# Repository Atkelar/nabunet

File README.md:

# nabunet - Modem and Network Specifications
My idea of a network backend for the "Nabu PC" - based on reverse engineering the old device and boot code...

The big question first: **why?** or **why not join any of the other similar projects?** simple: fun! For
me, most of the fun is the reverse engineering and coming-up-with-solutions phase. So joining some
other project here wouldn't do it for me... it is as simple as that. I hope that my view/take provides
something at least remotely unique and if public interest is low... I'll keep it to myself, but I'll
not stop just because "somebody else already did something similar" :)

## Revisions

  - Initial version, 2023-04-23
  - First steps Firmware/Config program, 2023-05-27
  - First public visible NabuNet server code, 2023-08-25

## References used

  - https://en.wikipedia.org/wiki/NABU_Network
  - https://bitsavers.org/pdf/nabu/Nabu_Computer_Technical_Manual_by_MJP.pdf

Other than those, the only information used was the original chips datasheets; Z-80, TR1863/1865, TMS9918A, AY-3-8910, 9637, 9639 and LS74-logic.

## Introduction

The basic idea for the "modem" is to hook up the Nabu Personal Computer (NPC, Nabu) to the internet.
Since Nabu is an 8-bit system with "just" 64k of RAM and the hookup has to be done via the built in
111kbit serial port, we cannot expect that the NPC is doing any heavy lifting (or any lifting) that
is required to connect to any IP based service directly these days, while still having enough
resources for any functional useful program left. The encryption code and state data alone is probably
eating up all of that RAM.

The modem should - IMHO - also be kept as simple as possible, ideally just forwarding any request
and response to an upstream server. But, at the least, do that already in an encrypted format, so
it supports direct internet connections via established, modern and available connectivity.

So, my idea in a nutshell: do all the required processing in a web service, where resources are plenty,
and let the modem do a very basic, simple translation of the requests/responses.

## High Level Operation

### Booting

The NPC "boots" into a 4k ROM module, although there seem to be 8k versions prepared too. Not sure if
these are ever implemented...

The ROM will initialize the support chips, do a functional check on all components (RAM, ROM, Sound, 
Keyboard and Modem chips) and then start to talk with the modem.

The first request to the modem are (assumed to be) initialization and synchronization commands.

The next command sent will reply with a flag bit either set or cleared to indicate if the modem has
the "channel code" set. This will tune the original cable modem to the appropriate channel but is
only kept in RAM. So a cold boot of the modem will not have that info.

If the modem is lacking the channel code, the NPC prompts the user to enter one. This is a five
digit hex code (00000 to FFFFF) but the last digit is a checksum, resulting in 65536 possible
channels to pick from. No range validation is performed here, and "all zero" is a valid code
that passes the checksum.

Once the channel code is entered, it is sent to the modem and the NPC waits for confirmation.

If either checksum or modem ack fails, the user is prompted to re-enter the code.

Once the modem has the channel code set, the NPC will request the "main program" as a sequence
of blocks. The buffer size that is set aside for loading them led to the assumption that
these blocks are up to 512 bytes in length each, with 16 bytes header and 2 bytes checksum
at the end.

The checksum is a derivative of the CRC-16 CCITT checksum, sometimes referred to as the "BAD"
implementation.

The only header bit used by boot loader is the "completed" bit, that indicates that the transferred
block was the last one of the sequence. Until that one is set, all blocks (without the header!)
are moved into RAM to offset 140Dh and on.

Note that the blocks can have arbitrary sizes, the "end of block" is signalled with a terminating
"10h" byte, followed by any other byte than "10h", with "0E1h" indicating success. Thus, the byte
sequence "10h E1h" terminates the block. To include a "10h" byte inside the payload, it has to
be escaped, i.e. "10h 10h" results in one "10h" byte to be loaded and checksum'd.

Once all blocks are received, the ROM is copied into the same RAM address and turned off, making
the byte range R/W from regular RAM but keeping the ROM code intact for rebooting the system. 
Execution is then passed to address 140Fh - note that it is two bytes AFTER the load offset and 
a rather odd address to start from...

### Boot loader code and "OS" idea...

To use the built in boot loader, we have to make use of the channel code somehow; my idea is to 
have the "00000" code provide a basic "initialize modem parameters" program. This is easy to
remember and can be used to set up the internet facing parameters, like server address to use,
SSID and key for WiFi, IP config for wired... these type of things.

Once set up, the modem can "pretend" to know the channel code, thus skipping the prompt.

To re-configure the modem, it should have a type of "reset" button; while a simple modem
reboot would serve the same purpose, I think it's a better idea to allow storing the modem
config in NVRAM somewhere to avoid the rather lengthy server/IP config every time...

The program provided for a known channel ID can then already be a "core OS", provided either
in parts or completely by the selected server.

### Security?!

Note: Any mandatory login or authentication beyond the server configuration is.. well...
taking away from the immersion of "ye-old-device". To keep the server somewhat secure and
proper suited for a modern internet with lots of bad players, the access to the information
available via the modem is considered "mostly read only" and "public"!

Once the modem is connected to the server with the proper credentials validated, the modem
will run with a simple "shared access token" against that server. This is by no means
"secure" and thus no highly sensitive information should ever be stored inside that 
environment! I'm talking personal information like credit card numbers and similar things.

Passing such information through the network to a server sided "callback" that does not
store anything inside the NPC accessible ranges should be fine, since the modem would
connect to the server via TLS... This still needs a proper security analysis of the
finished system though, so better assume that anything you enter into an application
will eventually become "public".

### Servers...

It is possible to use "physical" and "logical" servers. In order to function, the 
"channel zero" initialization has to point the modem to a physical server. During the
setup and configuration phase, that server can tell the modem if it supports "virtual"
servers. To keep the specs simple, there can be up to "FFF0h" virtual servers defined
per physical server, the numbers 1-F being reserved for "internal servers" if this
feature is enabled on the physical server... I'm thinking of "developer" and "diag"
servers mostly... If the physical server does NOT support virtual servers, it is
automaticalls assumed to be a single pre-selected virtual server for the rest of this
specification.

### Virtual Server

Each virtual server is a walled off environment, akin to a cable network. The main
purpose is to provide individual OS kernels during the boot process.

To switch to a differnet virtual server, a special reboot command is needed to tell
the modem to "forget" the current channel code. When the user is then prompted to
re-type the channel code, they can either use 00000 to go to the physical configuration
or any other number - if supported - to switch to another virtual server. The ROM
code doesn't have that provision to "force selection", this has to be done with
a flag in the modem;

I am also considering to have a "Nabu compatible" mode that keeps the communication 
between NPC and Modem 100% compatible with the original protocol, but that depends 
on me FINDING the specs for that protocol first... the problem here is that I don't
know if the original software would have an option to re-enter the channel code?
At worst case, the modem reset button would have to be used...

### DOS or not DOS?

The specs call the OS "DOS" for "Downloadable OS"... in contrast to the integrated
OS that boots the system. I am working on a reasonable implementation for simple
access to the different screen modes, sound chip and peripherals like the printer
port. My goal is to keep that OS below at least the 32k boundary, so the upper 32k
would always be available for program code. This doesn't sound like much, but keep
in mind that "loading a block from tape" or similar can now be considered "load
a block from the internet" at speeds that these devices are not used to. I think
almost any program can be made like that; The final decision on the memory 
requirements of the OS kernel are not set yet, so it might as well be much more.

Programs that make use of that "standard OS" could have simplified load code
provided, with a program browser as an initial app loaded from the server...

### R/W access?

A downside of the original NPC was the lack of storage space. But this is the age
of "cloud computing"... as much as I personally dislike that concept, it does
fit well with this system. During connection of the NPC with the server, personal
user info can be provided (think user/password) and when successful, the server
can provide storage space for that account. Note that the physical server can
choose if that space applies to logical servers and what part is server specific...
NPC doesn't see that difference. This would allow programs like - e.g. - a BASIC
interpreter to save/load programs from a "virtual disk" with ease.

To keep the stored information as secure as possible, the server will allow access
based on an access policy (private, server only, public) based on "virtual disk"
units. This would allow sharing information or keeping it private.

The resulting security model would however make it possible to use a guessed or
hijacked token to write to or just erase that information... to safeguard against
that possibility, a "snapshot" based system should be implemented on the server,
where these snapshots are invisible to the NPC and only controllable via the regular
internet facing, browser based management UI of your account. This should mitigate
any "attack" to the "less secure" data inside your Nabu Storage...

### Server software

Once sufficiently mature - i.e. as soon as it works at least a little bit :) - the 
server software along with the core OS will be published here as an open source 
project.

The overall concept would see it that anybody can code against the NPC and provide
their applications to the server(s) running this software.

I am - naturally - looking into hosting one of these myself as a "central default"
server...

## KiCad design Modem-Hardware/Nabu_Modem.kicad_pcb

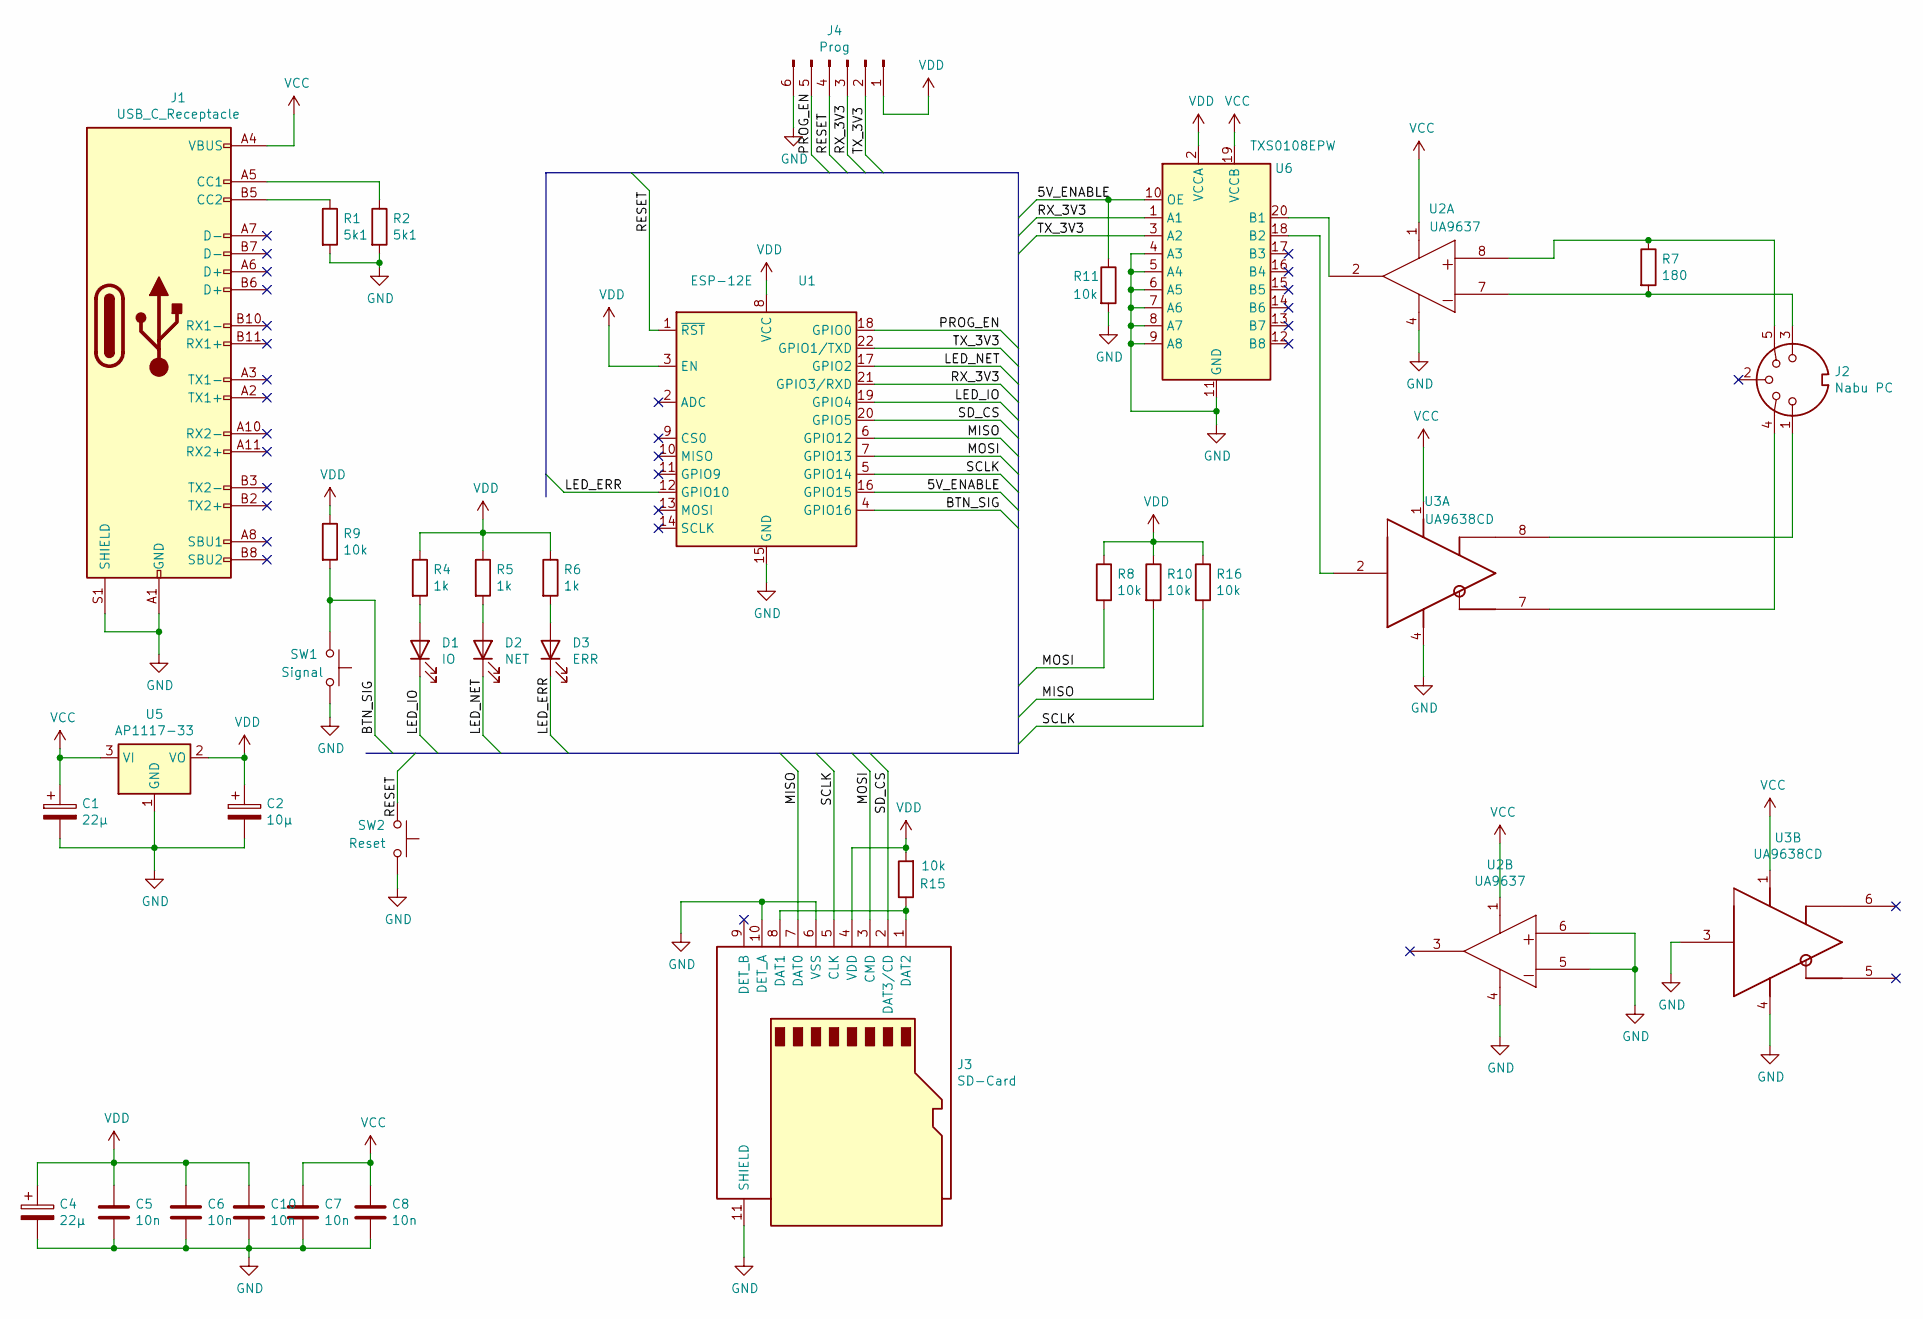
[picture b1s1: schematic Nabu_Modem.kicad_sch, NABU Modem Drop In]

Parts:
C1, C4: 22µ; C_2512_6332Metric_Pad1.52x3.35mm_HandSolder
C2: 10µ; C_2512_6332Metric_Pad1.52x3.35mm_HandSolder
C5, C6, C7, C8, C10: 10n; C_0603_1608Metric_Pad1.05x0.95mm_HandSolder
D1: IO; LED_0603_1608Metric
D2: NET; LED_0603_1608Metric
D3: ERR; LED_0603_1608Metric
J1: USB_C_Receptacle; USB_C_Receptacle_Amphenol_12401548E4-2A-X
J2: Nabu PC; MIDI_DIN5-B
J3: SD-Card; microSD_A
J4: Prog; PinHeader_2x03_P2.54mm_Vertical
R1, R2: 5k1; R_0603_1608Metric
R4, R5, R6: 1k; R_0603_1608Metric
R7: 180; R_0603_1608Metric
R8, R9, R10, R11, R15, R16: 10k; R_0603_1608Metric
SW1: Signal; SW_PUSH_6mm_H4.3mm
SW2: Reset; SW_PUSH_6mm_H4.3mm
U1: ESP-12E
U2: UA9637; DIP-8_W7.62mm
U3: UA9638CD; DIP-8_W7.62mm
U5: AP1117-33; SOT-223-3_TabPin2
U6: TXS0108EPW; TSSOP-20_4.4x6.5mm_P0.65mm

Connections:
/5V_ENABLE: R11.1, U1.16 (GPIO15), U6.10 (OE)
/BTN_SIG: R9.2, SW1.1, U1.4 (GPIO16)
/LED_ERR: D3.1 (K), U1.12 (GPIO10)
/LED_IO: D1.1 (K), U1.19 (GPIO4)
/LED_NET: D2.1 (K), U1.17 (GPIO2)
/MISO: J3.7 (DAT0), R10.2, U1.6 (GPIO12)
/MOSI: J3.3 (CMD), R8.2, U1.7 (GPIO13)
/PROG_EN: J4.5, U1.18 (GPIO0)
/RESET: J4.4, SW2.1, U1.1 (~RST)
/RX_3V3: J4.3, U1.21 (GPIO3/RXD), U6.1 (A1)
/SCLK: J3.5 (CLK), R16.2, U1.5 (GPIO14)
/SD_CS: J3.2 (DAT3/CD), U1.20 (GPIO5)
/TX_3V3: J4.2, U1.22 (GPIO1/TXD), U6.3 (A2)
GND: C1.2, C2.2, C4.2, C5.2, C6.2, C7.2, C8.2, C10.2, J1.A1 (GND), J1.A12 (GND), J1.B1 (GND), J1.B12 (GND), J1.S1 (SHIELD), J3.6 (VSS), J3.10 (DET_A), J3.11 (SHIELD), J4.6, R1.2, R2.2, R11.2, SW1.2, SW2.2, U1.15 (GND), U2.4 (GND), U2.5 (IN-), U2.6 (IN+), U3.3 (IN), U3.4 (GND), U5.1 (GND), U6.4 (A3), U6.5 (A4), U6.6 (A5), U6.7 (A6), U6.8 (A7), U6.9 (A8), U6.11 (GND)
unnamed: D1.2 (A), R4.2
unnamed: D2.2 (A), R5.2
unnamed: D3.2 (A), R6.2
unnamed: J1.A5 (CC1), R2.1
unnamed: J1.B5 (CC2), R1.1
unnamed: J2.1, U3.8 (OUTB)
unnamed: J2.3, R7.2, U2.7 (IN-)
unnamed: J2.4, U3.7 (OUTA)
unnamed: J2.5, R7.1, U2.8 (IN+)
unnamed: J3.1 (DAT2), J3.8 (DAT1), R15.1
unnamed: U2.2 (OUT), U6.20 (B1)
unnamed: U3.2 (IN), U6.18 (B2)
VCC: C1.1, C7.1, C8.1, J1.A4 (VBUS), J1.A9 (VBUS), J1.B4 (VBUS), J1.B9 (VBUS), U2.1 (VCC), U3.1 (VCC), U5.3 (VI), U6.19 (VCCB)
VDD: C2.1, C4.1, C5.1, C6.1, C10.1, J3.4 (VDD), J4.1, R4.1, R5.1, R6.1, R8.1, R9.1, R10.1, R15.2, R16.1, U1.3 (EN), U1.8 (VCC), U5.2 (VO), U6.2 (VCCA)

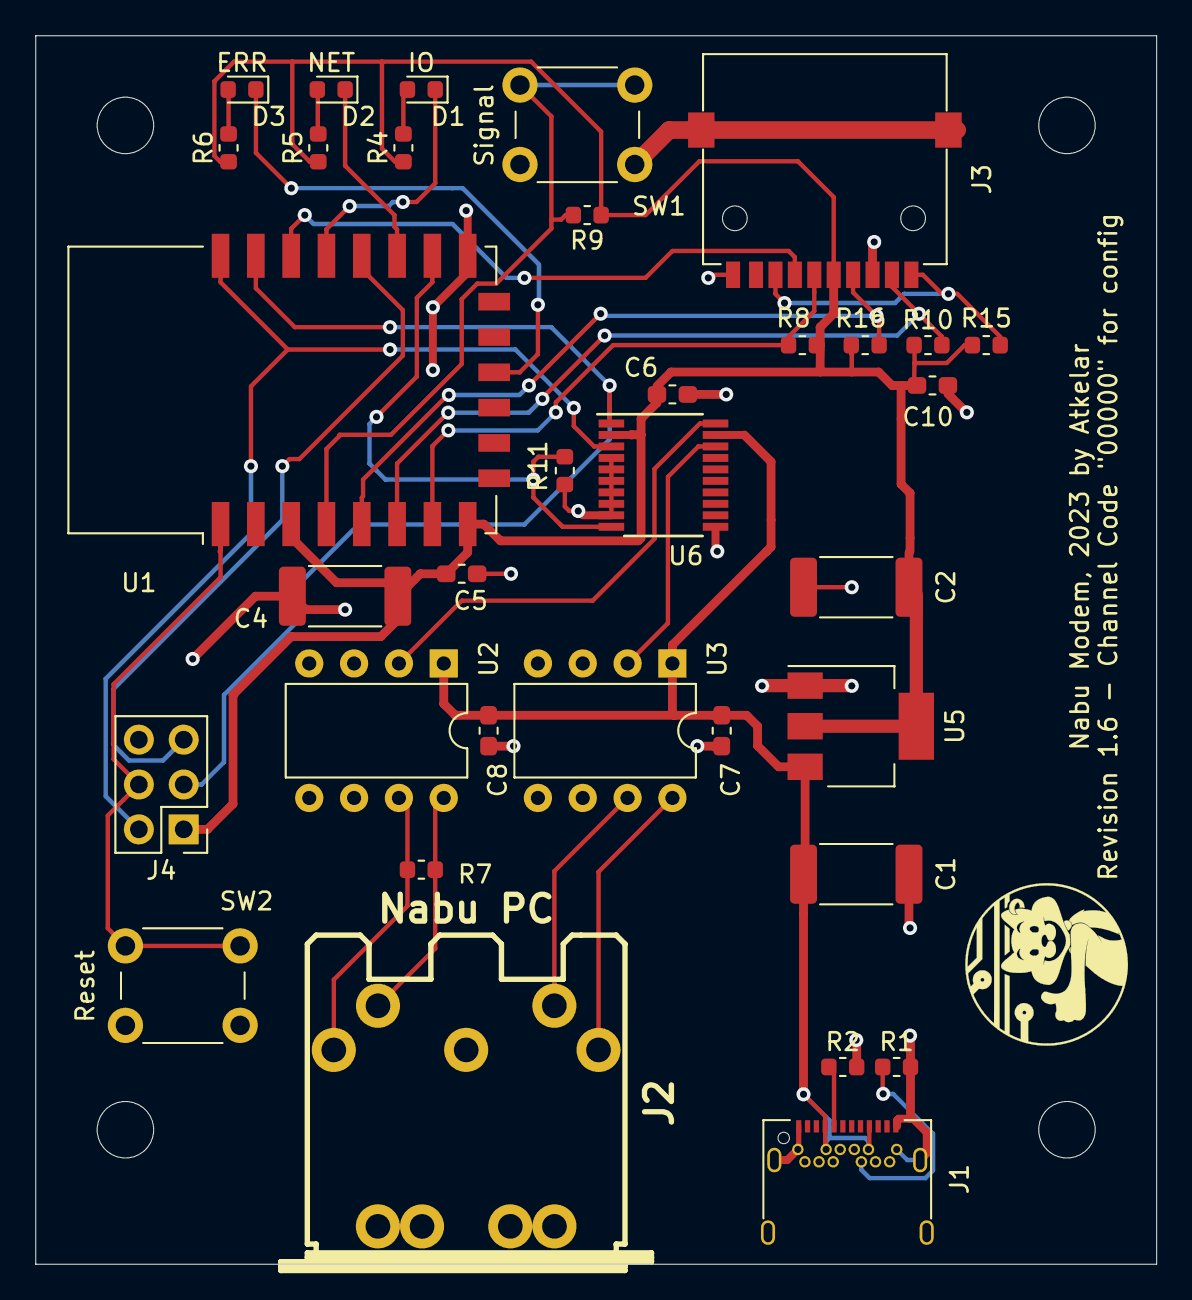
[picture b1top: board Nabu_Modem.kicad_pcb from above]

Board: 2 copper layers, 63.5 x 69.6 mm, 34 parts (0 on the bottom side), 28 nets.

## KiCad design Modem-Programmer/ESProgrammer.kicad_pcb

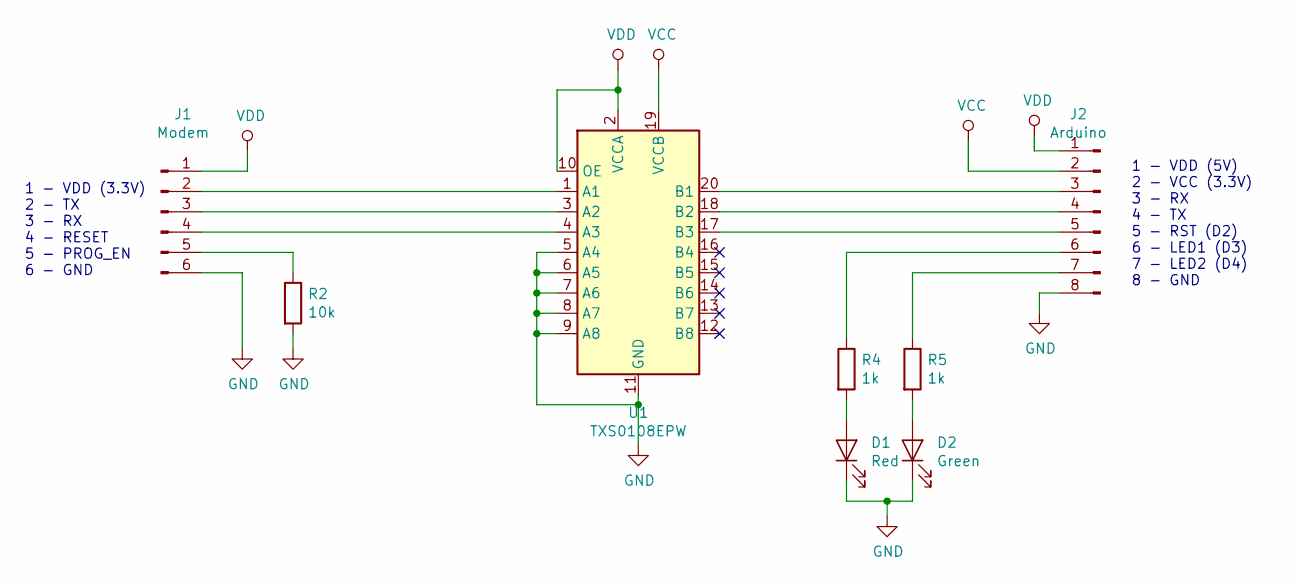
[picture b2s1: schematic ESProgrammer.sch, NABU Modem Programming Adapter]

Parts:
D1: Red; LED_0603_1608Metric_Pad1.05x0.95mm_HandSolder
D2: Green; LED_0603_1608Metric_Pad1.05x0.95mm_HandSolder
J1: Modem; PinSocket_2x03_P2.54mm_Horizontal
J2: Arduino; PinHeader_2x04_P2.54mm_Vertical
R2: 10k; R_0603_1608Metric_Pad1.05x0.95mm_HandSolder
R4, R5: 1k; R_0603_1608Metric_Pad1.05x0.95mm_HandSolder
U1: TXS0108EPW; TSSOP-20_4.4x6.5mm_P0.65mm

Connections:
GND: D1.1 (K), D2.1 (K), J1.6, J2.8, R2.2, U1.5 (A4), U1.6 (A5), U1.7 (A6), U1.8 (A7), U1.9 (A8), U1.11 (GND)
unnamed: D1.2 (A), R4.2
unnamed: D2.2 (A), R5.2
unnamed: J1.2, U1.1 (A1)
unnamed: J1.3, U1.3 (A2)
unnamed: J1.4, U1.4 (A3)
unnamed: J1.5, R2.1
unnamed: J2.3, U1.20 (B1)
unnamed: J2.4, U1.18 (B2)
unnamed: J2.5, U1.17 (B3)
unnamed: J2.6, R4.1
unnamed: J2.7, R5.1
VCC: J2.2, U1.19 (VCCB)
VDD: J1.1, J2.1, U1.2 (VCCA), U1.10 (OE); also elsewhere on the board

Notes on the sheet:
1 - VDD (3.3V) 2 - TX 3 - RX 4 - RESET 5 - PROG_EN 6 - GND
1 - VDD (5V) 2 - VCC (3.3V) 3 - RX 4 - TX 5 - RST (D2) 6 - LED1 (D3) 7 - LED2 (D4) 8 - GND

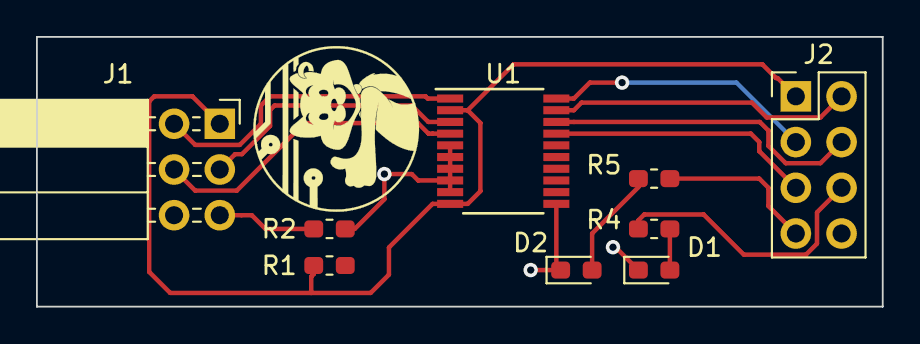
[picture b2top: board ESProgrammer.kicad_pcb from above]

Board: 2 copper layers, 47.0 x 15.0 mm, 9 parts (0 on the bottom side), 14 nets.

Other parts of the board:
R1: 10k; R_0603_1608Metric_Pad1.05x0.95mm_HandSolder

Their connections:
VDD: R1.1; also elsewhere on the board

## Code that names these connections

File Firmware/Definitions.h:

#ifndef NABUNETDEFINITIONSH
#define NABUNETDEFINITIONSH

// version number of firmware, for reporting... Maxmimum 16 chars!
// must be defined before any includes.
#define NABUNET_MODEM_FIRMWARE_VERSION "1.0.0 beta"



// LED status pins
#define PIN_LED_ERR 10
#define PIN_LED_NET 2
#define PIN_LED_IO 4

// Active high or low?
#define LED_ON 0    // LOW
#define LED_OFF 1   // HIGH

// ms delay for blinking signals. Must be less than 1000.
#define BLINK_DELAY 250

// Pins 12, 13, 14 are HSPI and should connect up to the SD Card
// IO Pin 5 is left for SD CS pin...
#define PIN_SD_CS 5

// pin 15 MUST be pulled low, othewise boot fails! Use it for output of 5V enable active high signal.
#define PIN_FIVEV_ENABLE 15


// "Signal" button, pulled high, active LOW.
#define PIN_SIGNAL 16

// (Error) signals are "blink codes" for the error LED
#define ERROR_SIGNAL_LOCALSERVERFAILD 2  // SD card based server was requested but didn't work out. Missing or bad files, broken card...
#define ERROR_SIGNAL_WIFIFAILED 3   // WiFi was configured, but has failed to connect to the remote server.
#define ERROR_SIGNAL_NOSERVER 4     // No server available; Both WiFi and Local server are not available.
#define ERROR_SIGNAL_FATAL_COM_ERROR 5  // the modem communication failed in an unexpected way.
#define ERROR_SIGNAL_REMOTE_CONN_FAILED 6 // remote server didn't reply or replied out of bounds
#define ERROR_SIGNAL_UPDATEFAILED 7 // Firmware update failed.

// the maximum send/receive buffer sizes
// tx buffer might need up to 512bytes + spare for 
// fully escaped loader block. Be sure to make them at leaset that size!
#define HCCA_BUFFER_SIZE 1024


// The filename on the SD card that is used to push a new config image to the internal storage.
const char BootImageFileName[] = "/nabuboot.img";
const char FirmwareImageFileName[] = "/nabufirm.img";
const char FirmwareTempFileName[] = "/nabu!ota.img";

// The internal filenames for the SPIFFS files to hold the config boot image. Two names to 
// alternate between 1 and 2, so a failed update will not brick the modem.
#define IMAGEFILE_1 "/cfgimg.1"
#define IMAGEFILE_2 "/cfgimg.2"



#endif

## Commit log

2023-04-23 Update README.md
    Updated readme file
2023-04-23 Update README.md
    Clarified the "why" inside the text
2023-04-23 Update README.md
    Added references.
2023-04-28 Added info about ROM research
2023-04-28 Uploaded boot flow chart
2023-04-28 Added embedded flowchart...
2023-05-05 Added first "hello world" sample source...
2023-05-27 Updated and added the first revision/idea of the config program...
2023-05-27 Added first test version of the firmware...
2023-05-27 Added hardware design.
2023-05-27 Added user doc PDF
2023-06-04 Updated with first modem commands
2023-06-05 First communication success to modem; listing WiFi networks works!
2023-06-15 Added logo asset
2023-07-02 Split firmware into multiple files/classes (buggy, but compiles)
2023-07-02 Fixed lots of issues after the CPP split, still not "perfect" but it boots again.
2023-08-25 Initial revision for Server; first "public" beta version!
2023-08-25 Added Karpour to the credits
2023-08-25 Updated config program
2023-08-25 Fixed vscode folder location
2023-08-25 Added Mail template manipulation via the NAPI interface and module
2023-08-25 Minor content update
2023-08-28 Fixed minor typos and issues. Added PS functions
2023-08-28 Fixed script analyzer warnings (as far as public methods are concerned)
2023-08-28 Updated package metadata
2023-08-28 Updated typo in module exports
2023-08-28 Added WebSocket troubleshooter...
2023-10-26 Updated for KiCAD 7
2023-10-26 Added VS Code arduino support, Fixed typo in filename and BlinkyStat code
2023-10-26 Fixed constructor args
2023-10-26 Added download and update code for firmware
2023-10-26 Tested: config/firmware image assets upload and clear via PS
2024-05-07 Updated user list, fixed last code update to compile.
2024-05-07 Updated cmdlet definitions for return types.
2024-05-07 Updated library verions
2024-05-08 Added mail diagnostics feature.
2024-05-08 Incorporated better UserAgent in admin script
2024-05-08 Remvoed vscode folder
2024-05-08 Updated copyright year
2024-05-08 Bumped PS version just in case
2024-05-08 Delete .vscode directory
    should be private to any dev; missed in gitignore...
2024-05-08 Fixed gitignore
